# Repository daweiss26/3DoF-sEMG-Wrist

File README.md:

# Orbita3D Setup Instructions

---

## Prerequisites

You need the following installed on your system:

* **Rust:** Used for compiling the kinematics SDK
* **Python (v3.12 Preferred):** Runs the controller

*Note: These instructions use python and pip commands. You may need to use python3 or pip3 depending on your setup.*

---

## Virtual Environment

It is recommended to create a virtual environment to store compiled packages

*Note: If using PowerShell, you may need to run ```
Set-ExecutionPolicy -ExecutionPolicy RemoteSigned -Scope Process``` first if activation is disabled.*

Create virtual environment (.venv recommended: Other environment names may require file changes such as run_camera_demo.bat)
```
python -m venv .venv
```

Activate virtual environment
```
.venv\Scripts\activate // Windows
source .venv/bin/activate // Mac/Linux
```

---

## Installation

Install the dependencies in the requirements.txt file:
```
pip install -r requirements.txt
```

Then install the Orbita3D package. Inside ```orbita3d_control/orbita3d_c_api```, run:
```
pip install -e .
```

---

## Firmware

Upload the Orbitarduinamixel project to your Generic STM32G4 Series device. Custom-installed libraries should be included in the project.

You may need to add the following .json file for additional boards in the Board Manager:
```
https://github.com/stm32duino/BoardManagerFiles/raw/main/package_stmicroelectronics_index.json
```

The libraries installed:
* **[Simple FOC](https://docs.simplefoc.com/):** by Simplefoc
* **[SimpleFOCDrivers](https://docs.simplefoc.com/):** by Simplefoc
* **[Dynamixel2Arduino](https://github.com/ROBOTIS-GIT/dynamixel2arduino):** by ROBOTIS
* **[Bolder Flight Systems BMI088](https://github.com/bolderflight/bmi088-arduino):** by Brian Taylor

---

## Use

*If using VSCode (recommended), ensure the project contains a ```.vscode``` file with:*
```
{
    "python-envs.defaultEnvManager": "ms-python.python:venv",
    "python.terminal.useEnvFile": true
}
```
Or, in your terminal, ```".:./src:./src/controller:./src/util"``` to your PYTHONPATH environment variable, such as with ```export PYTHONPATH=".:./src:./src/controller:./src/util:$PYTHONPATH"``` for Mac/Linux. For Windows, ```run_camera_demo.bat``` should take care of this.

If using Windows: running ```run_camera_demo.bat``` should work. *Note: You may need to change the specific virtual environment listed in the .bat file if you are using something different from .venv*

If using Mac/Linux: simply run a demo script from the project root directory such as ```python src/orbita_abh_camera.py```

*Note: If using a demo script, you will need to change the Ability Hand serial port in ```src/orbita_abh_camera.py``` and the Orbita3D serial port in ```config/default.yaml``` based upon your device setup. You will likely also need to alter the camera index in ```src/orbita_abh_camera.py``` depending on your setup.*

* **orbita_abh_camera.py:** Uses camera landmarks
* **orbita_emg.py:** Uses muscular signal and a residual TCN model
* **orbita_emg_krr.py:** Uses muscular signal and a kernel ridge regression model
* **task:** Contains landmarker tasks
* **config:** Contains .yaml files for Orbita3D setup. *Contains the serial port to use, which is determined by your specific device.*
* **orbita3d_control:** Contains kinematics for Orbita3D control.
* **firmware:** Contains Arduino code for Orbita3D
* **src/controller:** Contains controller classes for Orbita3D and Ability Hand
* **src/data_collection:** Contains tools for determining electromechanical delay and collecting data
* **src/train:** Contains tools for training muscular signal decoders using collected data
* **src/util:** Contains utilities such as the pose landmarker and coordinate transformer classes

---

## Sources

* **[Orbita3D](https://github.com/pollen-robotics/Orbita_3d_R1):** Original actuator design
* **[Orbita3D Control](https://github.com/pollen-robotics/orbita3d_control):** Generates the kinematics SDK
* **[Rustypot](https://github.com/pollen-robotics/rustypot):** Used to configure servos
* **[Ability Hand API](https://github.com/psyonicinc/ability-hand-api):** Reference on controlling PSYONIC Ability Hand

---

## Docker

You can also run the camera demo through Docker instead of creating a local Python environment if you are using Linux or an OS where Docker is not run on a virtual machine. The Docker image installs the Python dependencies from `requirements.txt`, builds and installs the local `orbita3d_control/orbita3d_c_api` package, and starts `src/orbita_abh_camera.py`.

### Build the image

From the project root, run:
```
docker build --platform linux/amd64 -t orbita-camera-demo .
```

### Run the container

The script needs access to your camera and, if you are controlling hardware, your serial devices. It also opens an OpenCV display window, so on Linux you will typically need to share your X11 socket. A common Linux example is:

```
docker run --platform linux/amd64 --rm -it \
  --device /dev/video0:/dev/video0 \
  --device /dev/ttyUSB0:/dev/ttyUSB0 \
  -e DISPLAY=$DISPLAY \
  -v /tmp/.X11-unix:/tmp/.X11-unix \
  orbita-camera-demo \
  --camera_index 0 \
  --hand_port /dev/ttyUSB0 \
  --orbita_config ./config/default.yaml
```

### Notes

* Update `config/default.yaml` so its `serial_port` matches the Orbita device inside the container, such as `/dev/ttyUSB1` or `/dev/serial/by-id/...`.
* The Ability Hand port is now configurable through `--hand_port`, which is helpful because Linux device names differ from macOS names such as `/dev/cu.usbserial-*`.
* If you only want to test the vision pipeline without connected hardware, you can add `--disable_wrist --disable_hand`.
* If your camera is exposed under a different device path or index, adjust `--device` and `--camera_index` accordingly.
* On macOS or Windows, Docker Desktop does not pass host cameras and serial devices into Linux containers as directly as native Linux does. For full hardware access, running the container on a Linux host is the simplest path.

### Pass different script arguments

Anything placed after the image name is forwarded to `src/orbita_abh_camera.py`. For example:

```
docker run --rm -it \
  --device /dev/video0:/dev/video0 \
  -e DISPLAY=$DISPLAY \
  -v /tmp/.X11-unix:/tmp/.X11-unix \
  orbita-camera-demo \
  --disable_wrist --disable_hand --camera_index 0 --use_elbow
```

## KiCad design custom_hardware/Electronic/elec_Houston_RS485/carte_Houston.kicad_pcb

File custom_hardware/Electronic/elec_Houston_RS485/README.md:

# Houston Electronic Board

Houston board is basically a STM32G4 microcontroller that focuses on driving 3 BLDC motors. It gets 3 Hall effects or encoders on motors and absolute positions behind reduction through SPI encoders.

<div align="center"></div>

## Basically
 - 50 x 54 mm
 - Powered in 3V3 through the large flat flexible connector J10
 - 5V should also be provided since it supplies encoders J11/21/31
 - Designed with KiCAD 6.0

## ST configuration

<div align="center"></div>

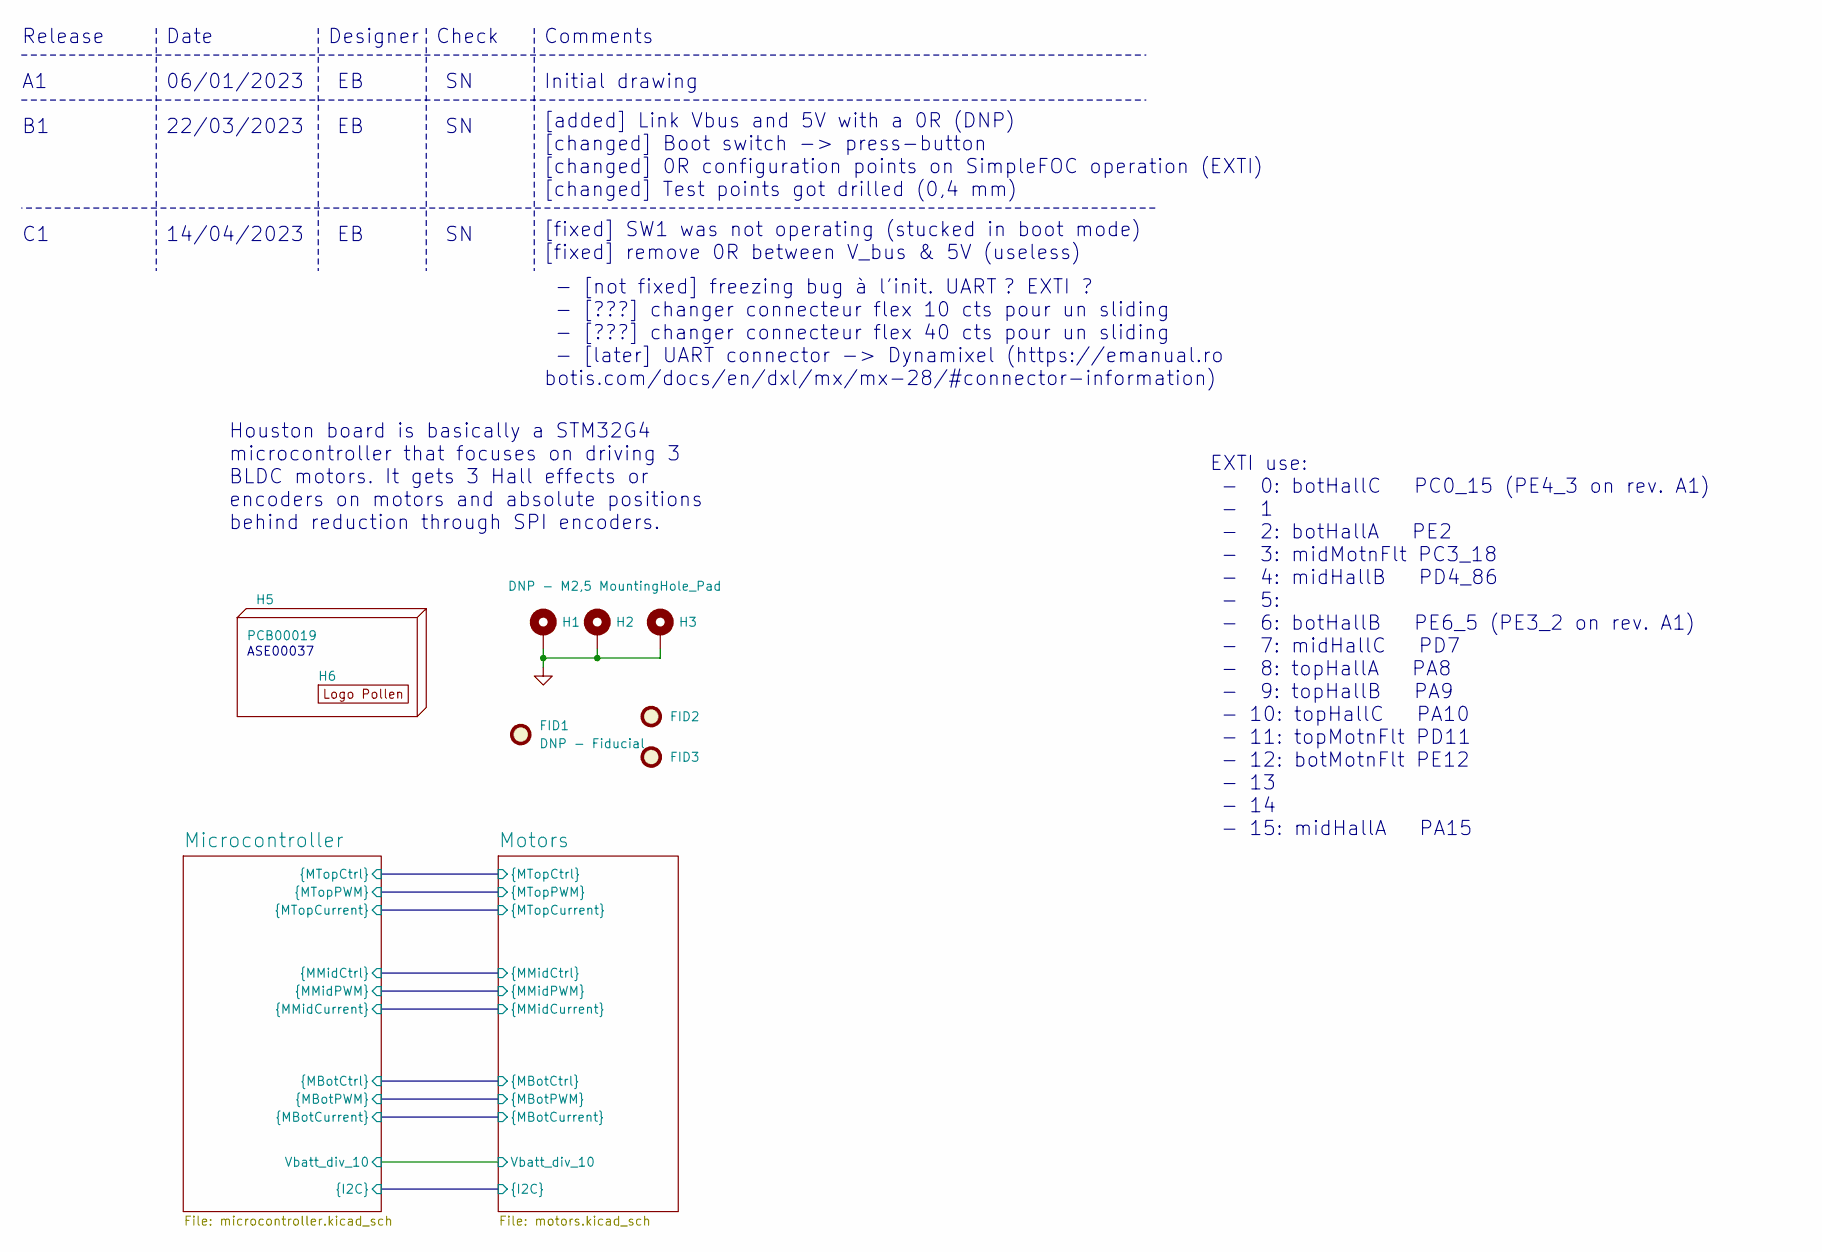
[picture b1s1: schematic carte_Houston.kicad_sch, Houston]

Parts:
FID1, FID2, FID3: DNP - Fiducial; Fiducial_1mm_Mask2mm
H1, H2, H3: DNP - M2,5 MountingHole_Pad; MountingHole_2.7mm_M2.5_DIN965_Pad_TopOnly
H5: PCB00019
H6: DNP - Logo Pollen 2021; Logo_Pollen_2021

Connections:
GND: H1.1, H2.1, H3.1; also elsewhere on the board

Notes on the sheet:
Date
Check
Release
[added] Link Vbus and 5V with a 0R (DNP) [changed] Boot switch -> press-button [changed] 0R configuration points on SimpleFOC operation (EXTI) [changed] Test points got drilled (0,4 mm)
ASE00037
22/03/2023
- [not fixed] freezing bug à l'init. UART ? EXTI ? - [???] changer connecteur flex 10 cts pour un sliding - [???] changer connecteur flex 40 cts pour un sliding - [later] UART connector -> Dynamixel (https://emanual.ro botis.com/docs/en/dxl/mx/mx-28/#connector-information)
Initial drawing
[fixed] SW1 was not operating (stucked in boot mode) [fixed] remove 0R between V_bus & 5V (useless)
EXTI use: - 0: botHallC PC0_15 (PE4_3 on rev. A1) - 1 - 2: botHallA PE2 - 3: midMotnFlt PC3_18 - 4: midHallB PD4_86 - 5: - 6: botHallB PE6_5 (PE3_2 on rev. A1) - 7: midHallC PD7 - 8: topHallA PA8 - 9: topHallB PA9 - 10: topHallC PA10 - 11: topMotnFlt PD11 - 12: botMotnFlt PE12 - 13 - 14 - 15: midHa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
Designer
14/04/2023
Houston board is basically a STM32G4 microcontroller that focuses on driving 3 BLDC motors. It gets 3 Hall effects or encoders on motors and absolute positions behind reduction through SPI encoders.
Comments
06/01/2023

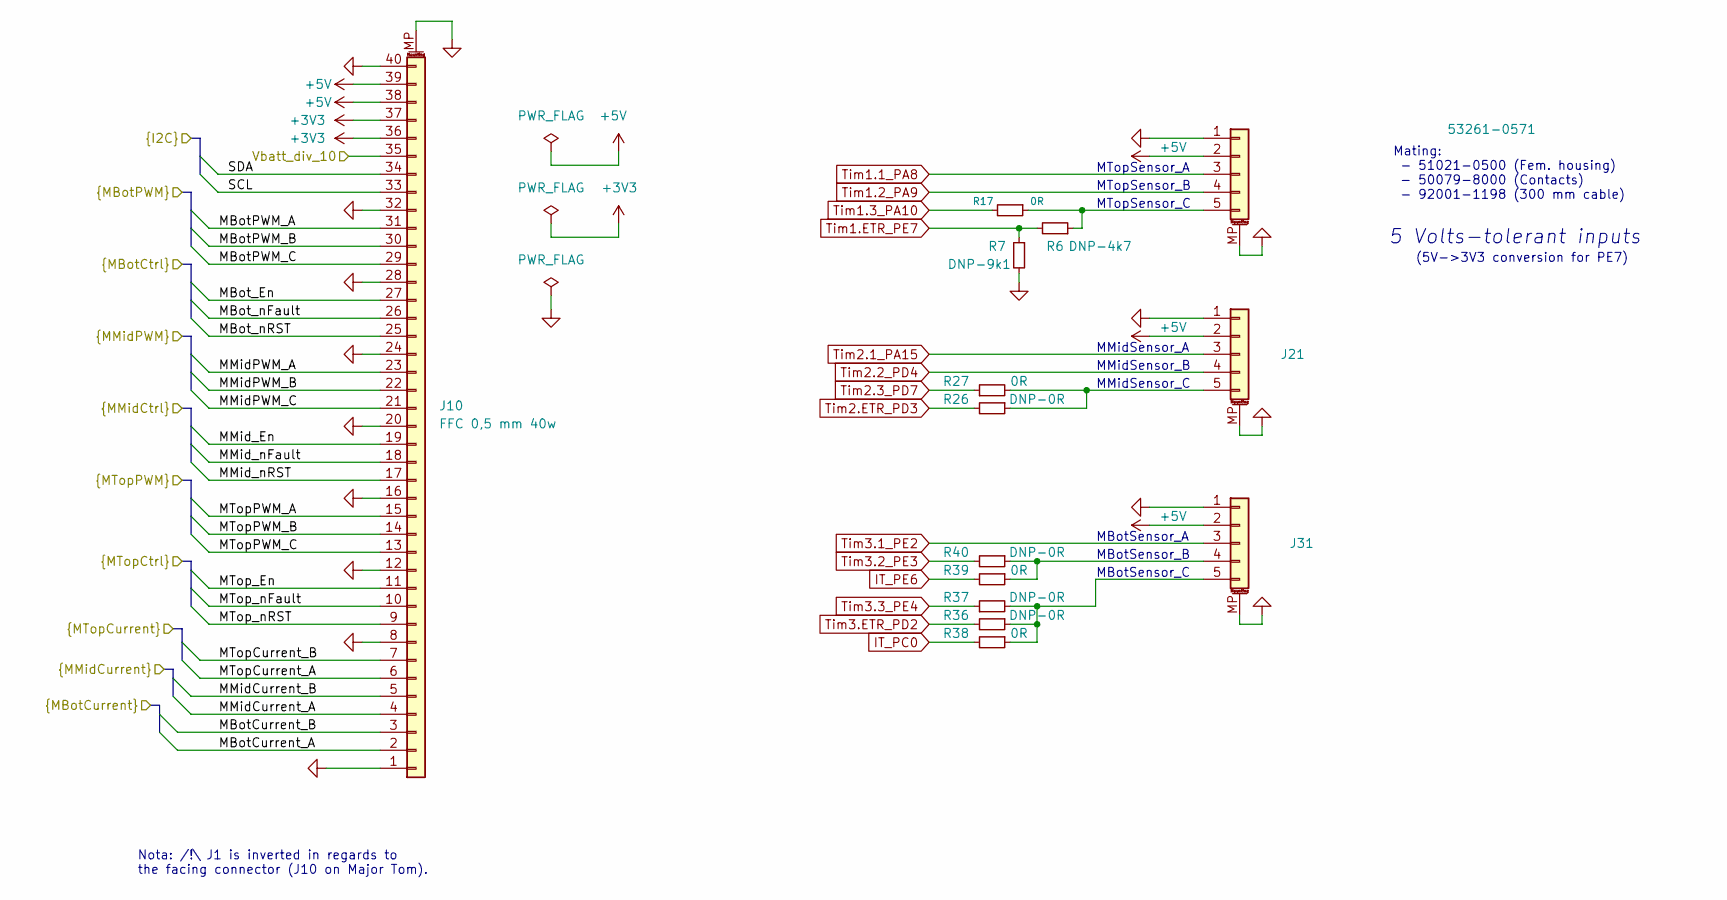
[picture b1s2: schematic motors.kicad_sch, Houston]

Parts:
J10: FFC 0,5 mm 40w; Hirose_FH12-40S-0.5SH_1x40-1MP_P0.50mm_Horizontal
J11: PicoBlade5; Molex_PicoBlade_53261-0571_1x05-1MP_P1.25mm_Horizontal
J21, J31: Pico5; Molex_PicoBlade_53261-0571_1x05-1MP_P1.25mm_Horizontal
R6: DNP-4k7; R_0603_1608Metric
R7: DNP-9k1; R_0603_1608Metric
R17, R27, R38, R39: 0R; R_0603_1608Metric
R26, R36, R37, R40: DNP-0R; R_0603_1608Metric

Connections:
+3V3: J10.36, J10.37; also elsewhere on the board
+5V: J10.38, J10.39, J11.2, J21.2, J31.2; also elsewhere on the board
/Microcontroller/MBotCurrent_A: J10.2; also elsewhere on the board
/Microcontroller/MBotCurrent_B: J10.3; also elsewhere on the board
/Microcontroller/MBotPWM_A: J10.31; also elsewhere on the board
/Microcontroller/MBotPWM_B: J10.30; also elsewhere on the board
/Microcontroller/MBotPWM_C: J10.29; also elsewhere on the board
/Microcontroller/MBot_En: J10.27; also elsewhere on the board
/Microcontroller/MBot_nFault: J10.26; also elsewhere on the board
/Microcontroller/MBot_nRST: J10.25; also elsewhere on the board
/Microcontroller/MMidCurrent_A: J10.4; also elsewhere on the board
/Microcontroller/MMidCurrent_B: J10.5; also elsewhere on the board
/Microcontroller/MMidPWM_A: J10.23; also elsewhere on the board
/Microcontroller/MMidPWM_B: J10.22; also elsewhere on the board
/Microcontroller/MMidPWM_C: J10.21; also elsewhere on the board
/Microcontroller/MMid_En: J10.19; also elsewhere on the board
/Microcontroller/MMid_nFault: J10.18; also elsewhere on the board
/Microcontroller/MMid_nRST: J10.17; also elsewhere on the board
/Microcontroller/MTopCurrent_A: J10.6; also elsewhere on the board
/Microcontroller/MTopCurrent_B: J10.7; also elsewhere on the board
/Microcontroller/MTopPWM_A: J10.15; also elsewhere on the board
/Microcontroller/MTopPWM_B: J10.14; also elsewhere on the board
/Microcontroller/MTopPWM_C: J10.13; also elsewhere on the board
/Microcontroller/MTop_En: J10.11; also elsewhere on the board
/Microcontroller/MTop_nFault: J10.10; also elsewhere on the board
/Microcontroller/MTop_nRST: J10.9; also elsewhere on the board
/Microcontroller/SCL: J10.33; also elsewhere on the board
/Microcontroller/SDA: J10.34; also elsewhere on the board
/Microcontroller/Vbatt_div_10: J10.35; also elsewhere on the board
GND: J10.1, J10.8, J10.12, J10.16, J10.20, J10.24, J10.28, J10.32, J10.40, J10.MP (MountPin), J11.1, J11.MP (MountPin), J21.1, J21.MP (MountPin), J31.1, J31.MP (MountPin), R7.2; also elsewhere on the board
IT_PC0: R38.2; also elsewhere on the board
IT_PE6: R39.2; also elsewhere on the board
unnamed: J11.5, R6.1, R17.1
unnamed: J21.5, R26.1, R27.2
unnamed: J31.4, R39.1, R40.1
unnamed: J31.5, R36.1, R37.2, R38.1
Tim1.1_PA8: J11.3; also elsewhere on the board
Tim1.2_PA9: J11.4; also elsewhere on the board
Tim1.3_PA10: R17.2; also elsewhere on the board
Tim1.ETR_PE7: R6.2, R7.1; also elsewhere on the board
Tim2.1_PA15: J21.3; also elsewhere on the board
Tim2.2_PD4: J21.4; also elsewhere on the board
Tim2.3_PD7: R27.1; also elsewhere on the board
Tim2.ETR_PD3: R26.2; also elsewhere on the board
Tim3.1_PE2: J31.3; also elsewhere on the board
Tim3.2_PE3: R40.2; also elsewhere on the board
Tim3.3_PE4: R37.1; also elsewhere on the board
Tim3.ETR_PD2: R36.2; also elsewhere on the board

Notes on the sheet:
MTopSensor_B
MBotSensor_A
MBotSensor_C
MTopSensor_C
MMidSensor_A
(5V->3V3 conversion for PE7)
MBotSensor_B
MTopSensor_A
MMidSensor_B
5 Volts-tolerant inputs
Nota: /!\ J1 is inverted in regards to the facing connector (J10 on Major Tom).
Mating: - 51021-0500 (Fem. housing) - 50079-8000 (Contacts) - 92001-1198 (300 mm cable)
MMidSensor_C

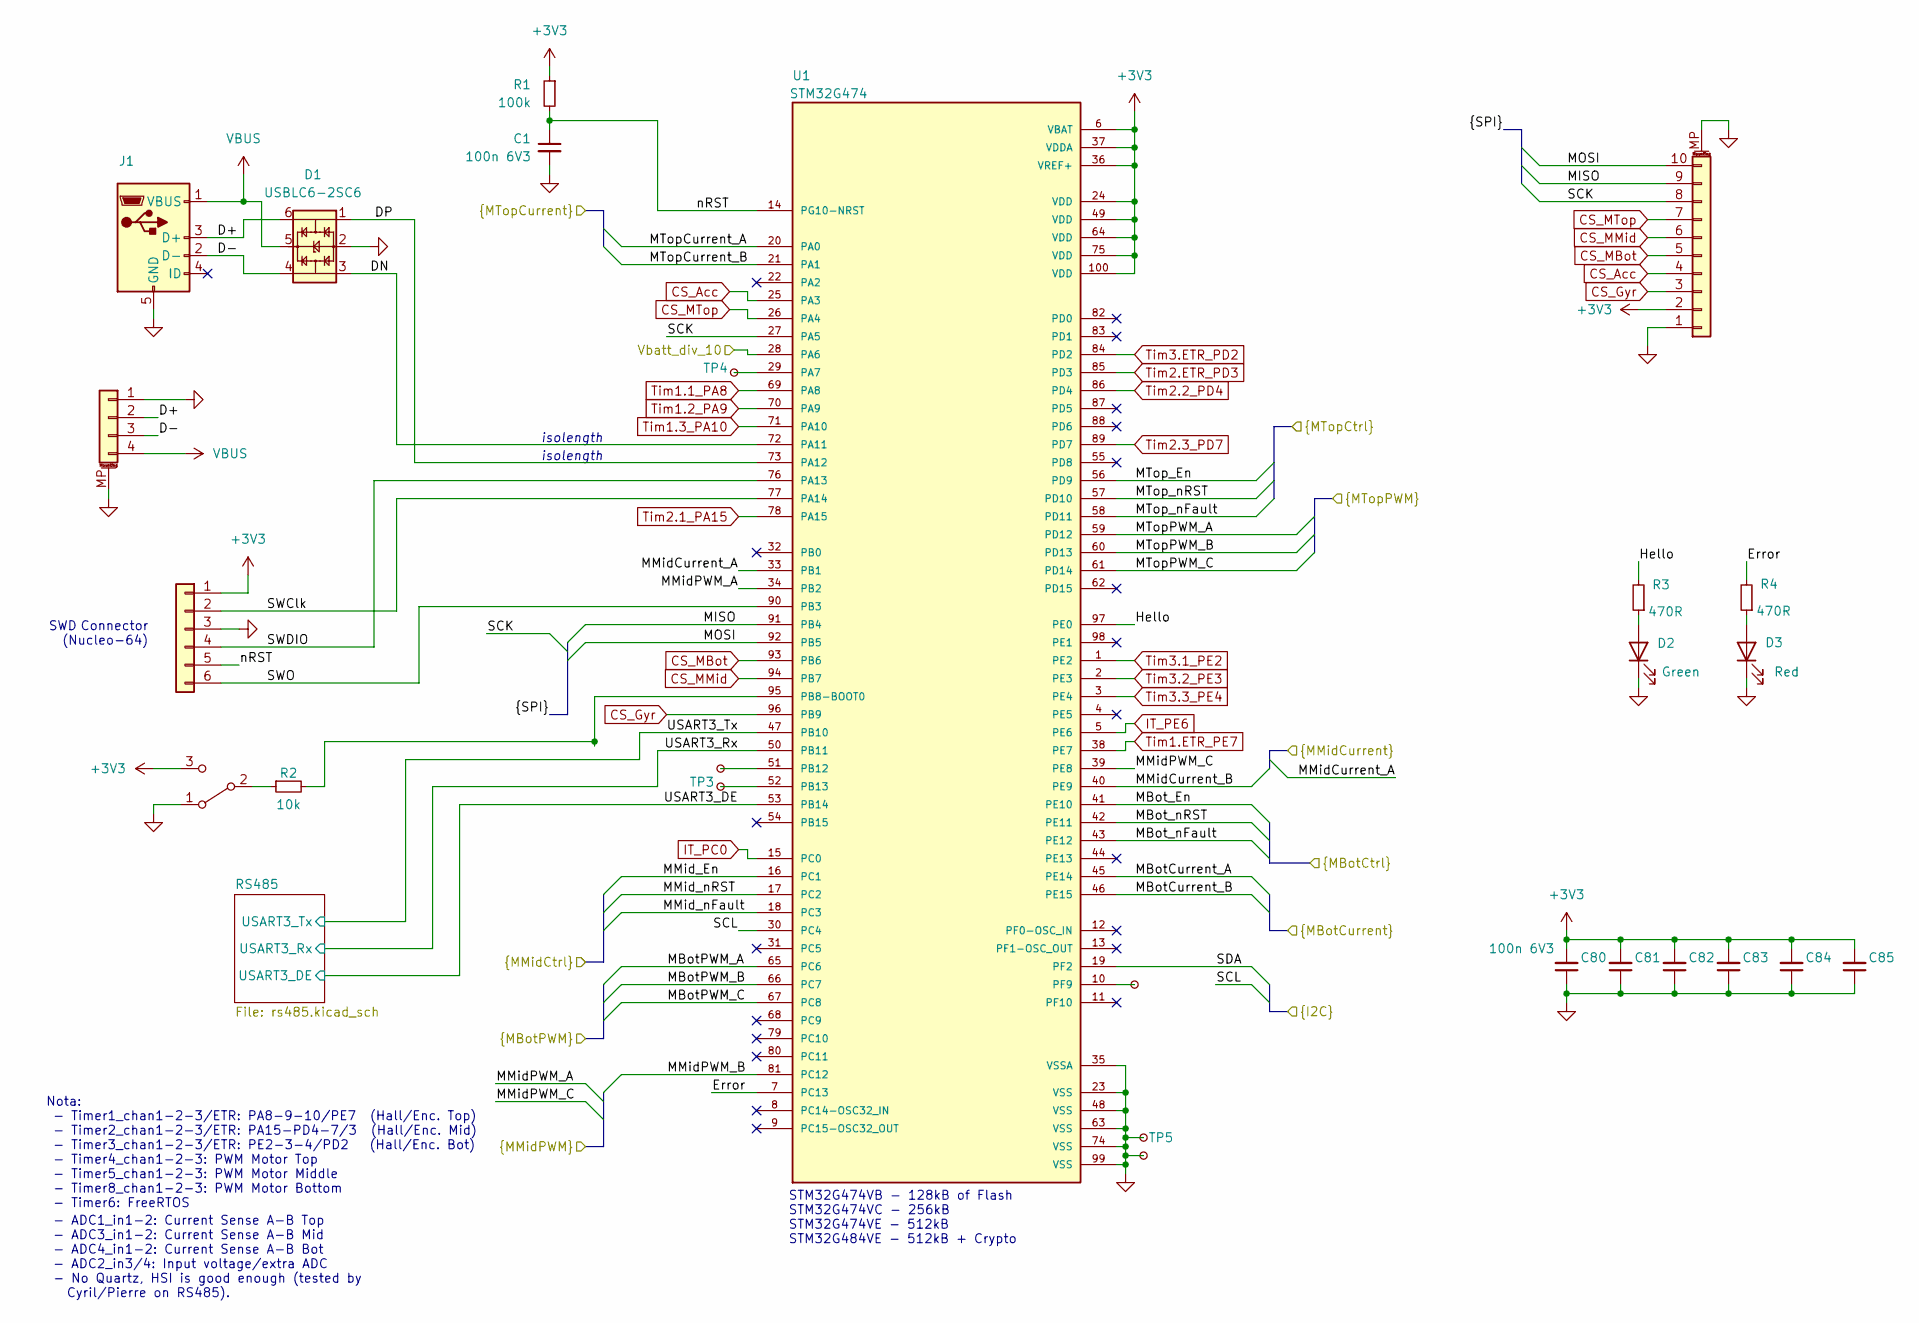
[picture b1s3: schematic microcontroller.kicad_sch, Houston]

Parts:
C1, C80, C81, C82, C83, C84, C85: 100n 6V3; C_0603_1608Metric
D1: USBLC6-2SC6; SOT23-6L
D2: Green; LED_0603_1608Metric_Pad1.05x0.95mm_HandSolder
D3: Red; LED_0603_1608Metric_Pad1.05x0.95mm_HandSolder
J1: 10118194-0001LF; Amphenol_10118194-0001LF
J3: SIL6; PinHeader_1x06_P2.54mm_Vertical
J4: PicoBlade4; Molex_PicoBlade_53398-0471_1x04-1MP_P1.25mm_Vertical
J5: Conn_01x10_MountingPin; Hirose_FH12-10S-0.5SH_1x10-1MP_P0.50mm_Horizontal
R1: 100k; R_0603_1608Metric
R2: 10k; R_0603_1608Metric
R3, R4: 470R; R_0603_1608Metric
SW1: SW_SPDT; SW_SPDT_CK-JS102011SAQN
TP1: DNP TestPoint_Small; TestPoint_THTPad_2.0x2.0mm_Drill1.0mm
TP2, TP6: DNP TestPoint_Small; TestPoint_Pad_D1.0mm
TP3, TP4, TP5: DNP - TestPoint_Small; TestPoint_THTPad_D1.0mm_Drill0.4mm
U1: STM32G474; QFP50P1600X1600X160-100N

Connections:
+3V3: C80.2, C81.2, C82.2, C83.2, C84.2, C85.2, J3.1, J5.2, R1.1, SW1.3 (C), U1.6 (VBAT), U1.24 (VDD), U1.36 (VREF+), U1.37 (VDDA), U1.49 (VDD), U1.64 (VDD), U1.75 (VDD), U1.100 (VDD); also elsewhere on the board
/Microcontroller/D+: D1.6, J1.3 (D+), J4.2
/Microcontroller/D-: D1.4, J1.2 (D-), J4.3
/Microcontroller/DN: D1.3, U1.72 (PA11)
/Microcontroller/DP: D1.1, U1.73 (PA12)
/Microcontroller/Error: R4.2, U1.7 (PC13)
/Microcontroller/Hello: R3.2, U1.97 (PE0)
/Microcontroller/MBotCurrent_A: U1.45 (PE14); also elsewhere on the board
/Microcontroller/MBotCurrent_B: U1.46 (PE15); also elsewhere on the board
/Microcontroller/MBotPWM_A: U1.65 (PC6); also elsewhere on the board
/Microcontroller/MBotPWM_B: U1.66 (PC7); also elsewhere on the board
/Microcontroller/MBotPWM_C: U1.67 (PC8); also elsewhere on the board
/Microcontroller/MBot_En: U1.41 (PE10); also elsewhere on the board
/Microcontroller/MBot_nFault: U1.43 (PE12); also elsewhere on the board
/Microcontroller/MBot_nRST: U1.42 (PE11); also elsewhere on the board
/Microcontroller/MISO: J5.9, U1.91 (PB4)
/Microcontroller/MMidCurrent_A: U1.33 (PB1); also elsewhere on the board
/Microcontroller/MMidCurrent_B: U1.40 (PE9); also elsewhere on the board
/Microcontroller/MMidPWM_A: U1.34 (PB2); also elsewhere on the board
/Microcontroller/MMidPWM_B: U1.81 (PC12); also elsewhere on the board
/Microcontroller/MMidPWM_C: U1.39 (PE8); also elsewhere on the board
/Microcontroller/MMid_En: U1.16 (PC1); also elsewhere on the board
/Microcontroller/MMid_nFault: U1.18 (PC3); also elsewhere on the board
/Microcontroller/MMid_nRST: U1.17 (PC2); also elsewhere on the board
/Microcontroller/MOSI: J5.10, U1.92 (PB5)
/Microcontroller/MTopCurrent_A: U1.20 (PA0); also elsewhere on the board
/Microcontroller/MTopCurrent_B: U1.21 (PA1); also elsewhere on the board
/Microcontroller/MTopPWM_A: U1.59 (PD12); also elsewhere on the board
/Microcontroller/MTopPWM_B: U1.60 (PD13); also elsewhere on the board
/Microcontroller/MTopPWM_C: U1.61 (PD14); also elsewhere on the board
/Microcontroller/MTop_En: U1.56 (PD9); also elsewhere on the board
/Microcontroller/MTop_nFault: U1.58 (PD11); also elsewhere on the board
/Microcontroller/MTop_nRST: U1.57 (PD10); also elsewhere on the board
/Microcontroller/SCK: J5.8, U1.27 (PA5)
/Microcontroller/SCL: U1.30 (PC4); also elsewhere on the board
/Microcontroller/SDA: U1.19 (PF2); also elsewhere on the board
/Microcontroller/SWClk: J3.2, U1.77 (PA14)
/Microcontroller/SWDIO: J3.4, U1.76 (PA13)
/Microcontroller/SWO: J3.6, U1.90 (PB3)
/Microcontroller/USART3_DE: U1.53 (PB14); also elsewhere on the board
/Microcontroller/USART3_Rx: U1.50 (PB11); also elsewhere on the board
/Microcontroller/USART3_Tx: U1.47 (PB10); also elsewhere on the board
/Microcontroller/Vbatt_div_10: U1.28 (PA6); also elsewhere on the board
/Microcontroller/nRST: C1.1, J3.5, R1.2, U1.14 (PG10-NRST)
CS_Acc: J5.4, U1.25 (PA3)
CS_Gyr: J5.3, U1.96 (PB9)
CS_MBot: J5.5, U1.93 (PB6)
CS_MMid: J5.6, U1.94 (PB7)
CS_MTop: J5.7, U1.26 (PA4)
GND: C1.2, C80.1, C81.1, C82.1, C83.1, C84.1, C85.1, D1.2, D2.1 (K), D3.1 (K), J1.5 (GND), J3.3, J4.1, J4.MP (MountPin), J5.1, J5.MP (MountPin), SW1.1 (A), TP1.1, TP5.1, U1.23 (VSS), U1.35 (VSSA), U1.48 (VSS), U1.63 (VSS), U1.74 (VSS), U1.99 (VSS); also elsewhere on the board
IT_PC0: U1.15 (PC0); also elsewhere on the board
IT_PE6: U1.5 (PE6); also elsewhere on the board
unnamed: D2.2 (A), R3.1
unnamed: D3.2 (A), R4.1
unnamed: R2.1, SW1.2 (B)
unnamed: TP4.1, U1.29 (PA7)
unnamed: R2.2, U1.95 (PB8-BOOT0)
unnamed: TP2.1, U1.51 (PB12)
unnamed: TP3.1, U1.52 (PB13)
unnamed: TP6.1, U1.10 (PF9)
Tim1.1_PA8: U1.69 (PA8); also elsewhere on the board
Tim1.2_PA9: U1.70 (PA9); also elsewhere on the board
Tim1.3_PA10: U1.71 (PA10); also elsewhere on the board
Tim1.ETR_PE7: U1.38 (PE7); also elsewhere on the board
Tim2.1_PA15: U1.78 (PA15); also elsewhere on the board
Tim2.2_PD4: U1.86 (PD4); also elsewhere on the board
Tim2.3_PD7: U1.89 (PD7); also elsewhere on the board
Tim2.ETR_PD3: U1.85 (PD3); also elsewhere on the board
Tim3.1_PE2: U1.1 (PE2); also elsewhere on the board
Tim3.2_PE3: U1.2 (PE3); also elsewhere on the board
Tim3.3_PE4: U1.3 (PE4); also elsewhere on the board
Tim3.ETR_PD2: U1.84 (PD2); also elsewhere on the board
VBUS: D1.5, J1.1 (VBUS), J4.4

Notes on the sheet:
Nota: - Timer1_chan1-2-3/ETR: PA8-9-10/PE7 (Hall/Enc. Top) - Timer2_chan1-2-3/ETR: PA15-PD4-7/3 (Hall/Enc. Mid) - Timer3_chan1-2-3/ETR: PE2-3-4/PD2 (Hall/Enc. Bot) - Timer4_chan1-2-3: PWM Motor Top - Timer5_chan1-2-3: PWM Motor Middle - Timer8_chan1-2-3: PWM Motor Bottom - Timer6: FreeRTOS
isolength
STM32G474VB - 128kB of Flash STM32G474VC - 256kB STM32G474VE - 512kB STM32G484VE - 512kB + Crypto
SWD Connector (Nucleo-64)
- ADC1_in1-2: Current Sense A-B Top - ADC3_in1-2: Current Sense A-B Mid - ADC4_in1-2: Current Sense A-B Bot - ADC2_in3/4: Input voltage/extra ADC - No Quartz, HSI is good enough (tested by Cyril/Pierre on RS485).

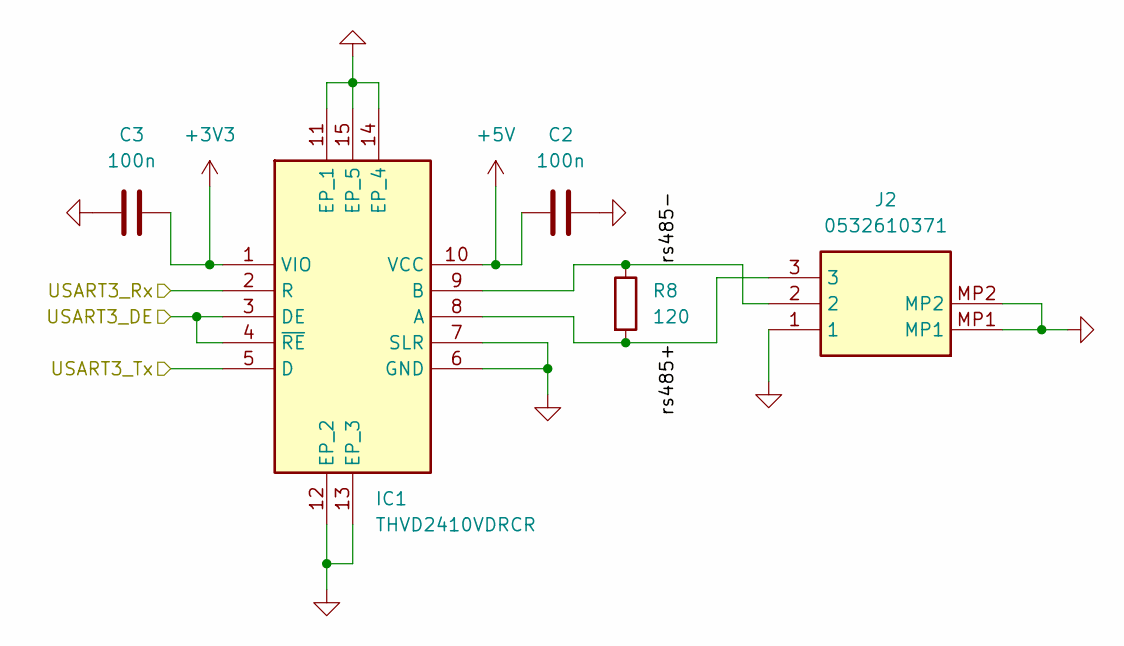
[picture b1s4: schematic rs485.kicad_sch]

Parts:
C2, C3: 100n; C_0402_1005Metric
IC1: THVD2410VDRCR; TPS259241DRCR; Manufacturer_Part_Number THVD2410VDRCR; Mouser Part Number 595-THVD2410VDRCR
J2: 0532610371; Manufacturer_Part_Number 0532610371
R8: 120; R_0402_1005Metric

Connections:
+3V3: C3.2, IC1.1 (VIO); also elsewhere on the board
+5V: C2.1, IC1.10 (VCC); also elsewhere on the board
/Microcontroller/RS485/rs485+: IC1.8 (A), J2.3, R8.2
/Microcontroller/RS485/rs485-: IC1.9 (B), J2.2, R8.1
/Microcontroller/USART3_DE: IC1.3 (DE), IC1.4 (~RE); also elsewhere on the board
/Microcontroller/USART3_Rx: IC1.2 (R); also elsewhere on the board
/Microcontroller/USART3_Tx: IC1.5 (D); also elsewhere on the board
GND: C2.2, C3.1, IC1.6 (GND), IC1.7 (SLR), IC1.11 (EP_1), IC1.12 (EP_2), IC1.13 (EP_3), IC1.14 (EP_4), IC1.15 (EP_5), J2.1, J2.MP1, J2.MP2; also elsewhere on the board

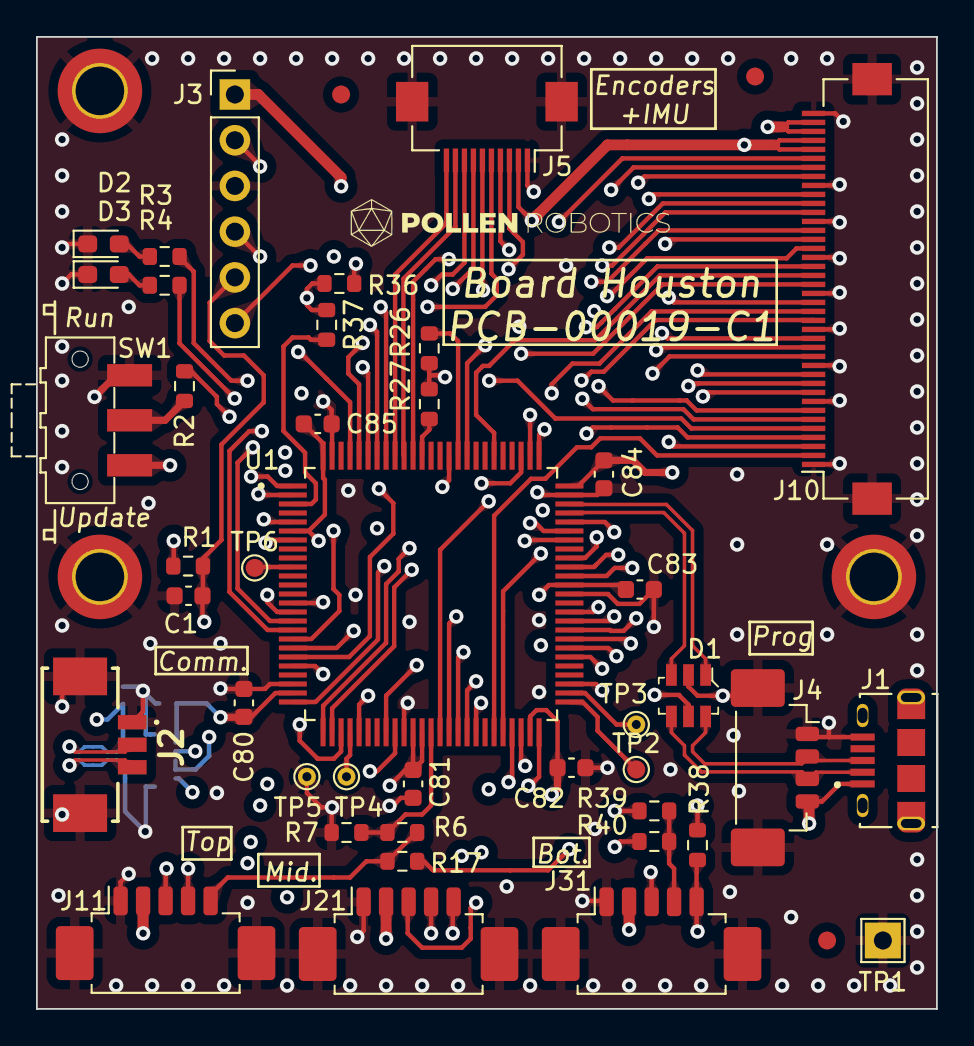
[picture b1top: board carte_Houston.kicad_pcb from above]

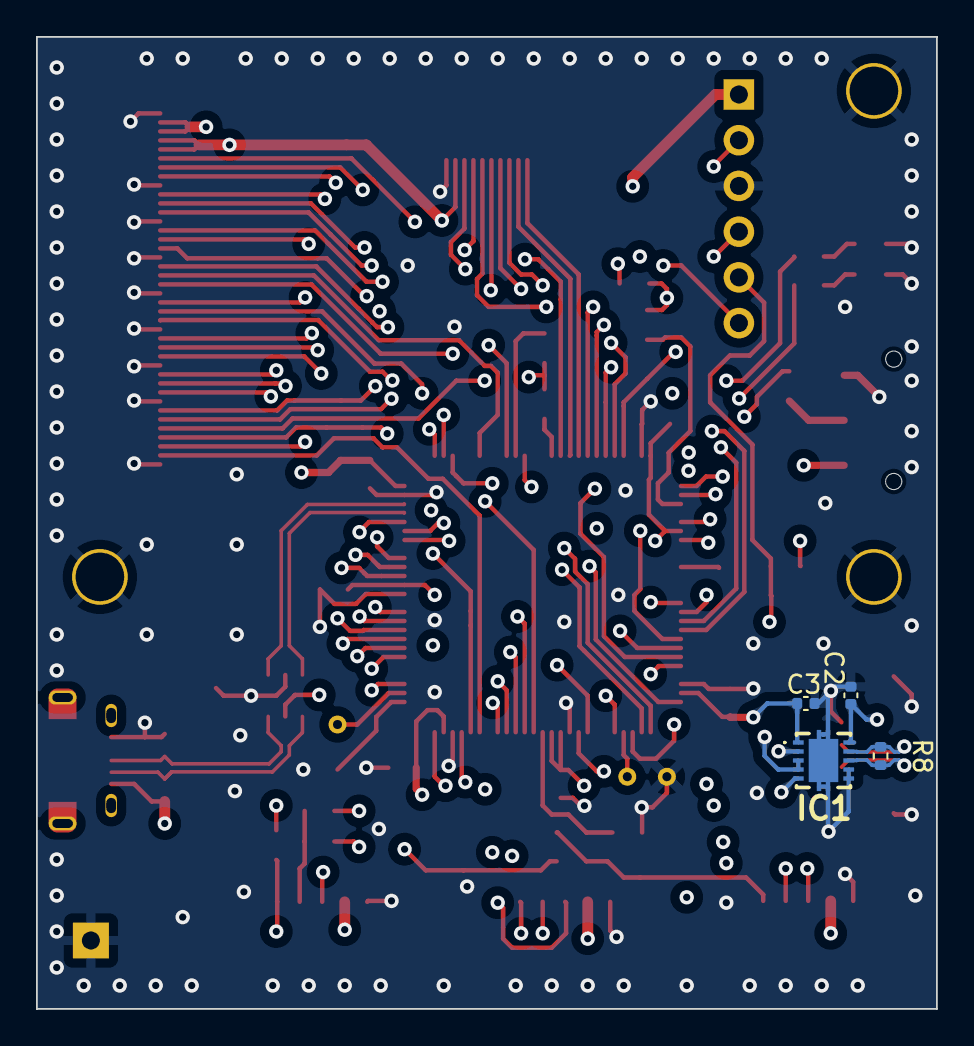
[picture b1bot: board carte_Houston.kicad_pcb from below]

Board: 4 copper layers, 50.0 x 54.0 mm, 52 parts (4 on the bottom side), 80 nets.

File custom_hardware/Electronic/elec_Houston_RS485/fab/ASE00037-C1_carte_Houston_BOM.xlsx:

ASE00037 | C1 | Houston | 45030
Ref. | Value | Description | Qtty | Man. | Man. Ref.
C1, C80, C81, C82, C83, C84, C85 | 100n 6V3 | Capa 0603 | 7 | TDK | CGA3E2X7R1H104K080AA
D1 | USBLC6-2SC6 | ESD Protection | 1 | STMicro | USBLC6-2SC6
D2 | Green | Green LED 0603 | 1 | Wurth | 150060VS75000
D3 | Red | Red LED 0603 | 1 | Wurth | 150060RS75000
H5 | PCB00019 | PCB | 1
J1 | 10118194-0001LF | USB Prog Connector | 1 | Amphenol FCI | 10118194-0001LF
J2 | Pico3 | Comm. Connector | 1 | Molex | 53261-0371
J3 | DNP - SIL6 | SWDebug Connector | 1 | Harwin | M20-9990646
J4 | Pico4 | Fake USB Connector | 1 | Molex | 53398-0471
J5 | FFC 0,5 mm 10w | Encoders/IMU Connector | 1 | Hirose | FH12-10S-0.5SH(55)
J11, J21, J31 | Pico5 | Comm. Connector | 3 | Molex | 53261-0571
J10 | FFC 0,5 mm 40w | Microcontroller Connector | 1 | Hirose | FH12-40S-0.5SH(55)
R1 | 100k | Res. 0603 | 1 | Yageo | RC0603FR-07100KL
R2 | 10k | Res. 0603 | 1 | Yageo | RC0603FR-0710KL
R3, R4 | 470R | Res. 0603 | 2 | Yageo | RC0603FR-07470RL
R6 | DNP-4k7 | Res. 0603 | 1
R7 | DNP-9k1 | Res. 0603 | 1
R17, R27, R38, R39 | 0R | Res. 0603 | 4 | Yageo | RC0603FR-070RL
R26, R36, R37, R40 | DNP-0R | Res. 0603 | 4
SW1 | SW_SPDT | Boot switch | 1 | C&K Switches | JS102011SAQN
U1 | STM32G474 | Microcontroller | 1 | STMicro | STM32G474VET6

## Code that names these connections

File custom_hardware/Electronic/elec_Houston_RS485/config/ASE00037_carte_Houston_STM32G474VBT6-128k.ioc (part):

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Mcu.Name=STM32G474V(B-C-E)Tx
Mcu.Package=LQFP100
Mcu.UserName=STM32G474VBTx
PA0.Mode=IN1-Single-Ended
PA0.Signal=ADC1_IN1
PA1.Mode=IN2-Single-Ended
PA1.Signal=ADC1_IN2
PA10.Signal=S_TIM1_CH3
PA11.Mode=Device
PA11.Signal=USB_DM
PA12.Mode=Device
PA12.Signal=USB_DP
PA13.Mode=Serial_Wire
PA13.Signal=SYS_JTMS-SWDIO
PA14.Mode=Serial_Wire
PA14.Signal=SYS_JTCK-SWCLK
PA15.Signal=S_TIM2_CH1
PA3.Signal=GPIO_Output
PA4.Signal=GPIO_Output
PA5.Mode=Full_Duplex_Master
PA5.Signal=SPI1_SCK
PA6.Mode=IN3-Single-Ended
PA6.Signal=ADC2_IN3
PA7.Mode=IN4-Single-Ended
PA7.Signal=ADC2_IN4
PA8.Signal=S_TIM1_CH1
PA9.Signal=S_TIM1_CH2
PB1.Mode=IN1-Single-Ended
PB1.Signal=ADC3_IN1
PB10.Mode=Asynchronous
PB10.Signal=USART3_TX
PB11.Mode=Asynchronous
PB11.Signal=USART3_RX
PB12.Signal=GPIO_Output
PB13.Signal=GPIO_Output
PB14.Signal=GPIO_Output
PB2.Signal=S_TIM5_CH1
PB3.Signal=SYS_JTDO-SWO
PB4.Mode=Full_Duplex_Master
PB4.Signal=SPI1_MISO
PB5.Mode=Full_Duplex_Master
PB5.Signal=SPI1_MOSI
PB6.Signal=GPIO_Output
PB7.Signal=GPIO_Output
PC1.Signal=GPIO_Output
PC12.Signal=S_TIM5_CH2
PC13.Signal=GPIO_Output
PC2.Signal=GPIO_Output
PC3.Signal=GPIO_Input
PC4.Mode=I2C
PC4.Signal=I2C2_SCL
PC6.Signal=S_TIM8_CH1
PC7.Signal=S_TIM8_CH2
PC8.Signal=S_TIM8_CH3
PD10.Signal=GPIO_Output
PD11.Signal=GPIO_Input
PD12.Signal=S_TIM4_CH1
PD13.Signal=S_TIM4_CH2
PD14.Signal=S_TIM4_CH3
PD2.Signal=S_TIM3_ETR
PD3.Signal=S_TIM2_ETR
PD4.Signal=S_TIM2_CH2
PD7.Signal=S_TIM2_CH3
PD9.Signal=GPIO_Output
PE0.Signal=GPIO_Output
PE10.Signal=GPIO_Output
PE11.Signal=GPIO_Output
PE12.Signal=GPIO_Input
PE14.Mode=IN1-Single-Ended
PE14.Signal=ADC4_IN1
PE15.Mode=IN2-Single-Ended
PE15.Signal=ADC4_IN2
PE2.Signal=S_TIM3_CH1
PE3.Signal=S_TIM3_CH2
PE4.Signal=S_TIM3_CH3
PE7.Signal=S_TIM1_ETR
PE8.Signal=S_TIM5_CH3
PE9.Mode=IN2-Single-Ended
PE9.Signal=ADC3_IN2
PF0-OSC_IN.Mode=I2C
PF0-OSC_IN.Signal=I2C2_SDA
RCC.HSE_VALUE=8000000
RCC.SYSCLKFreq_VALUE=168000000
RCC.SYSCLKSource=RCC_SYSCLKSOURCE_PLLCLK
board=custom

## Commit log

2026-04-09 figure generation for poster
2026-04-09 cleanup
2026-04-09 camera demo should be working with venv
2026-04-09 stop tracking pycache
2026-04-09 ignore ds_store
2026-04-09 use latest mediapipe
2026-04-09 seems to work with tensorflow now, don't fail on hand serial connect failure
2026-04-09 optional error on failure to connect
2026-04-09 same for wrist
2026-04-09 major refactor to make this a real project
2026-04-09 don't need poster stuff
2026-04-09 don't need serial, need pyserial
2026-04-10 emd working properly
2026-04-10 fix old scripts
2026-04-10 training data file name fix
2026-04-10 improved logging and instructions
2026-04-10 getting poster figure
2026-04-22 Update readme, add .bat file, and add firmware
2026-04-22 Add orbita3d_control
2026-04-22 update gitignore
2026-04-22 Remove uneeded files
2026-04-22 Fix bug where data collection is only sampling every 250ms, should be 50ms
2026-04-23 Dockerize
2026-04-23 docker process should work if you can pass the device
2026-05-01 Add custom hardware (electronics and parts)
2026-05-18 small changes
2026-05-18 don't need the split
2026-05-18 orbita_emg works for sure
